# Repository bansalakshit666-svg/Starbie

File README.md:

Starbie is a small motion controlled digital pet with minimal gameplay buttons. IYou can interact with it by physically moving the board.

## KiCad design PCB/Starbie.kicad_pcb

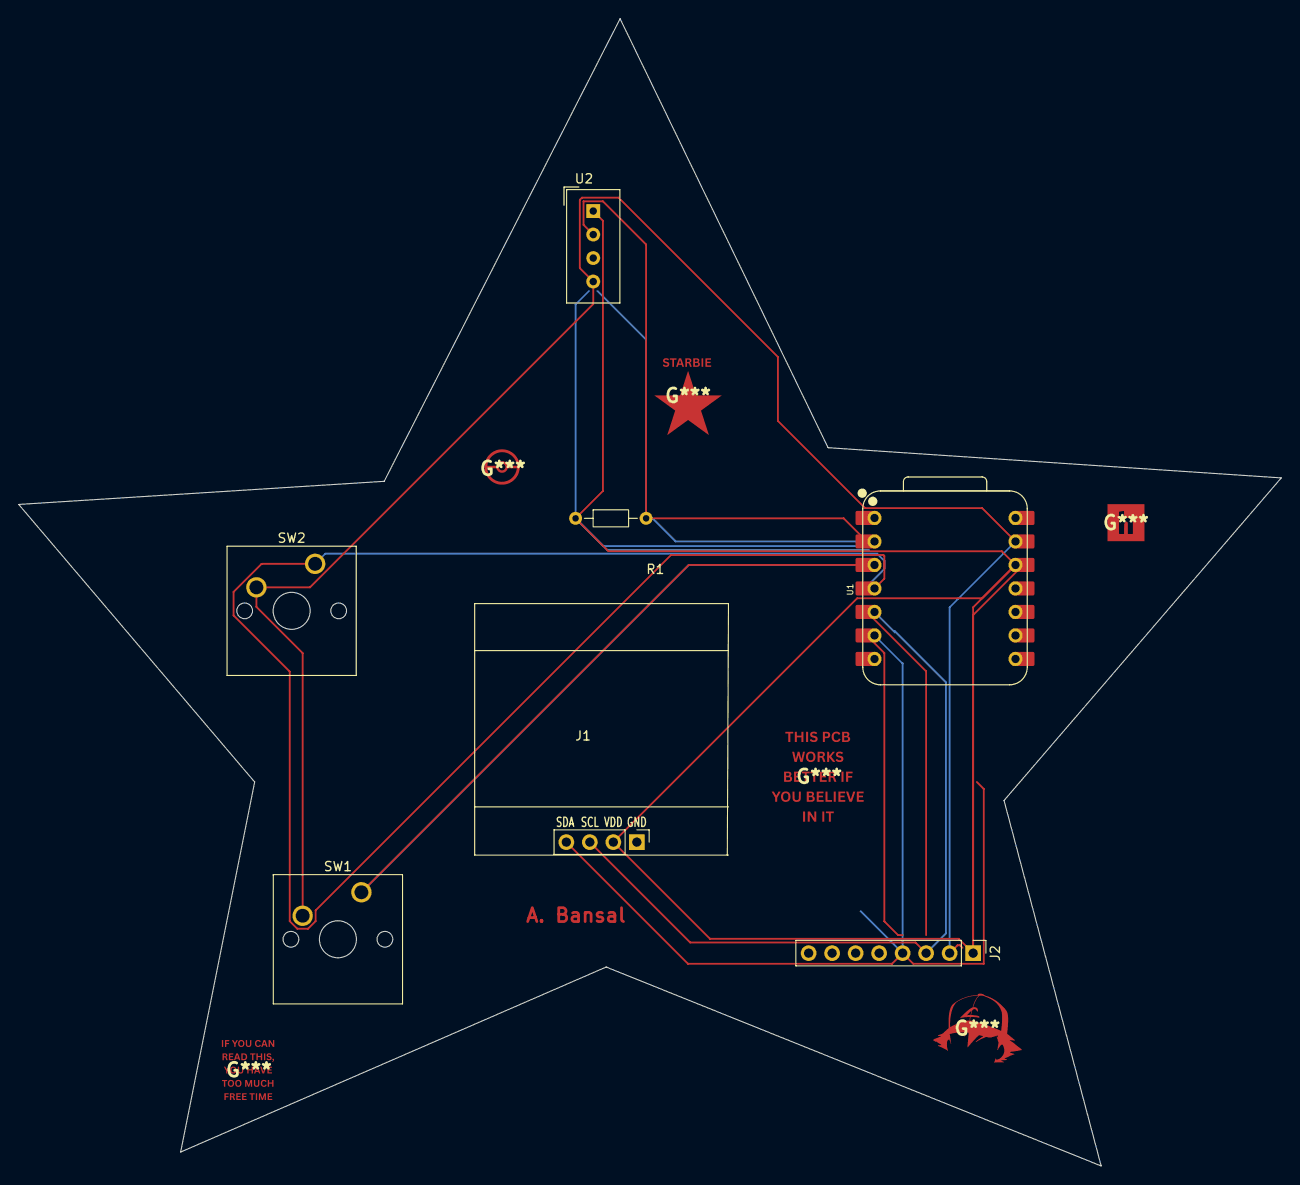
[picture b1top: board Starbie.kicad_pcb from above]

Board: 2 copper layers, 136.5 x 124.0 mm, 7 parts (0 on the bottom side), 7 nets.

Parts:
J1: Conn_01x04_Pin; Display_128x64_096_I2C
J2: Conn_01x08_Pin; PinHeader_1x08_P2.54mm_Vertical
R1: 10K; R_Axial_DIN0204_L3.6mm_D1.6mm_P7.62mm_Horizontal
SW1, SW2: SW_Push; SW_Cherry_MX_1.00u_PCB
U1: XIAO-ESP32-C3-SMD; XIAO-ESP32-C6-DIP
U2: DHT11; Aosong_DHT11_5.5x12.0_P2.54mm

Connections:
+3.3V: J1.2, J2.1, R1.1, U1.12 (3V3_OUT), U2.1 (VDD)
/DHT11 DATA: R1.2, U1.2 (D1), U2.2 (DATA)
/GPIO2: SW1.1, U1.3 (D2)
/GPIO3: SW2.1, U1.4 (D3)
/scl: J1.3, J2.3, U1.5 (D4)
/sda: J1.4, J2.4, U1.6 (D5)
GND: J2.2, SW1.2, SW2.2, U1.13 (GND), U2.4 (GND)
